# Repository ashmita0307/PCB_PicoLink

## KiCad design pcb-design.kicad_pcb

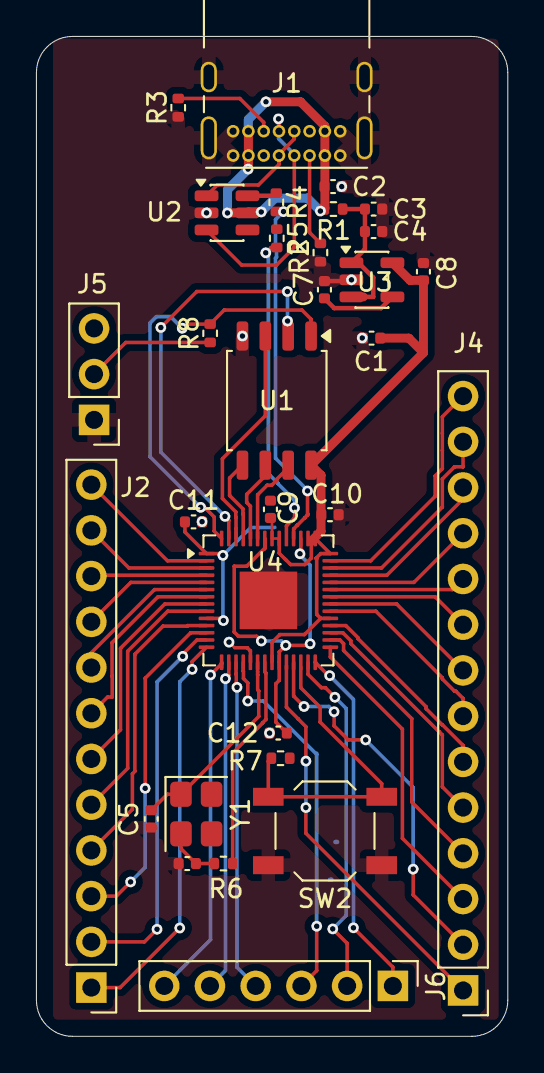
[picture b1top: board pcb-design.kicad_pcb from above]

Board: 2 copper layers, 26.2 x 55.5 mm, 31 parts (0 on the bottom side), 57 nets.

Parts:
C1: 0.1uF; C_0402_1005Metric
C2, C3, C7: 470n; C_0402_1005Metric
C4, C8: 10u; C_0402_1005Metric
C5, C6: 27pF; C_0402_1005Metric
C9, C10: 100 nF; C_0402_1005Metric
C11: 100nF; C_0402_1005Metric
C12: 1uF; C_0402_1005Metric
J1: USB_C_Receptacle_USB2.0_16P; USB_C_Receptacle_GCT_USB4085
J2: Conn_01x12; PinHeader_1x12_P2.54mm_Vertical
J4: Conn_01x14; PinHeader_1x14_P2.54mm_Vertical
J5: Conn_01x02; PinHeader_1x03_P2.54mm_Vertical
J6: Conn_01x06; PinHeader_1x06_P2.54mm_Vertical
R1: 0; R_0402_1005Metric
R2, R3: 5k1; R_0402_1005Metric
R4, R5: 27; R_0402_1005Metric
R6, R8: 1k; R_0402_1005Metric
R7: 10K; R_0402_1005Metric
SW2: SW_Push; SW_SPST_TL3342
U1: W25Q16JVSS; SOIC-8_5.3x5.3mm_P1.27mm
U2: USBLC6-2SC6; SOT-23-6
U3: SPX3819M5-L-3-3; SOT-23-5
U4: RP2040; QFN-56-1EP_7x7mm_P0.4mm_EP3.2x3.2mm
Y1: 12Mhz; Crystal_SMD_3225-4Pin_3.2x2.5mm

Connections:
+3V3: C1.1, C8.1, C9.1, C10.1, C11.1, U1.8 (VCC), U3.5 (OUT), U4.1 (IOVDD), U4.10 (IOVDD), U4.22 (IOVDD), U4.33 (IOVDD), U4.42 (IOVDD), U4.43 (ADC_AVDD), U4.44 (VREG_VIN), U4.48 (USB_VDD), U4.49 (IOVDD)
/+1V1: C12.2, U4.23 (DVDD), U4.45 (VREG_VOUT), U4.50 (DVDD)
/GPIO0: J2.12, U4.2 (GPIO0)
/GPIO1: J2.11, U4.3 (GPIO1)
/GPIO2: J2.10, U4.4 (GPIO2)
/GPIO3: J2.9, U4.5 (GPIO3)
/GPIO4: J2.8, U4.6 (GPIO4)
/GPIO5: J2.7, U4.7 (GPIO5)
/GPIO6: J2.6, U4.8 (GPIO6)
/GPIO7: J2.5, U4.9 (GPIO7)
/GPIO8: J2.4, U4.11 (GPIO8)
/GPIO9: J2.3, U4.12 (GPIO9)
/GPIO10: J2.2, U4.13 (GPIO10)
/GPIO11: J2.1, U4.14 (GPIO11)
/GPIO12: J6.6, U4.15 (GPIO12)
/GPIO13: J6.5, U4.16 (GPIO13)
/GPIO14: J6.4, U4.17 (GPIO14)
/GPIO15: J6.3, U4.18 (GPIO15)
/GPIO16: J6.2, U4.27 (GPIO16)
/GPIO17: J6.1, U4.28 (GPIO17)
/GPIO18: J4.3, U4.29 (GPIO18)
/GPIO19: J4.4, U4.30 (GPIO19)
/GPIO20: J4.5, U4.31 (GPIO20)
/GPIO21: J4.6, U4.32 (GPIO21)
/GPIO22: J4.7, U4.34 (GPIO22)
/GPIO23: J4.8, U4.35 (GPIO23)
/GPIO24: J4.9, U4.36 (GPIO24)
/GPIO25: J4.10, U4.37 (GPIO25)
/GPIO26/ADC0: J4.11, U4.38 (GPIO26/ADC0)
/GPIO27/ADC1: J4.12, U4.39 (GPIO27/ADC1)
/GPIO28/ADC2: J4.13, U4.40 (GPIO28/ADC2)
/GPIO29/ADC3: J4.14, U4.41 (GPIO29/ADC3)
/QSPI_SCLK: U1.6 (CLK), U4.52 (QSPI_SCLK)
/QSPI_SD0: U1.5 (DI/IO_{0}), U4.53 (QSPI_SD0)
/QSPI_SD1: U1.2 (DO/IO_{1}), U4.55 (QSPI_SD1)
/QSPI_SD2: U1.3 (~WP/IO_{2}), U4.54 (QSPI_SD2)
/QSPI_SD3: U1.7 (~HOLD/~RESET/IO_{3}), U4.51 (QSPI_SD3)
/QSPI_SS: R8.2, U1.1 (~CS), U4.56 (~QSPI_SS)
/SWCLK: J4.1, U4.24 (SWCLK)
/SWD: J4.2, U4.25 (SWDIO)
/USB_BOOT: J5.2, R8.1
/USB_DM: R4.2, U4.46 (USB_DM)
/USB_DP: R5.2, U4.47 (USB_DP)
/XIN: C5.1, U4.20 (XIN), Y1.1
/XOUT: R6.2, U4.21 (XOUT)
GND: C1.2, C2.2, C3.2, C4.2, C5.2, C6.1, C7.2, C8.2, C9.2, C10.2, C11.2, C12.1, J1.A1 (GND), J1.A12 (GND), J1.B1 (GND), J1.B12 (GND), J1.SH (SHIELD), J5.1, R2.1, R3.1, SW2.1, U1.4 (GND), U2.2 (GND), U3.2 (GND), U4.19 (TESTEN), U4.57 (GND)
unnamed: C6.2, R6.1, Y1.2
unnamed: J1.A5 (CC1), R2.2
unnamed: J1.B5 (CC2), R3.2
unnamed: J1.A6 (D+), J1.B6 (D+), U2.3 (I/O2)
unnamed: J1.A7 (D-), J1.B7 (D-), U2.1 (I/O1)
unnamed: R4.1, U2.6 (I/O1)
unnamed: R5.1, U2.4 (I/O2)
unnamed: C7.1, U3.4 (BP)
unnamed: R7.2, SW2.2, U4.26 (RUN)
VBUS: C2.1, J1.A4 (VBUS), J1.A9 (VBUS), J1.B4 (VBUS), J1.B9 (VBUS), R1.2, U2.5 (VBUS)
VBUSF: C3.1, C4.1, R1.1, U3.1 (IN), U3.3 (EN)

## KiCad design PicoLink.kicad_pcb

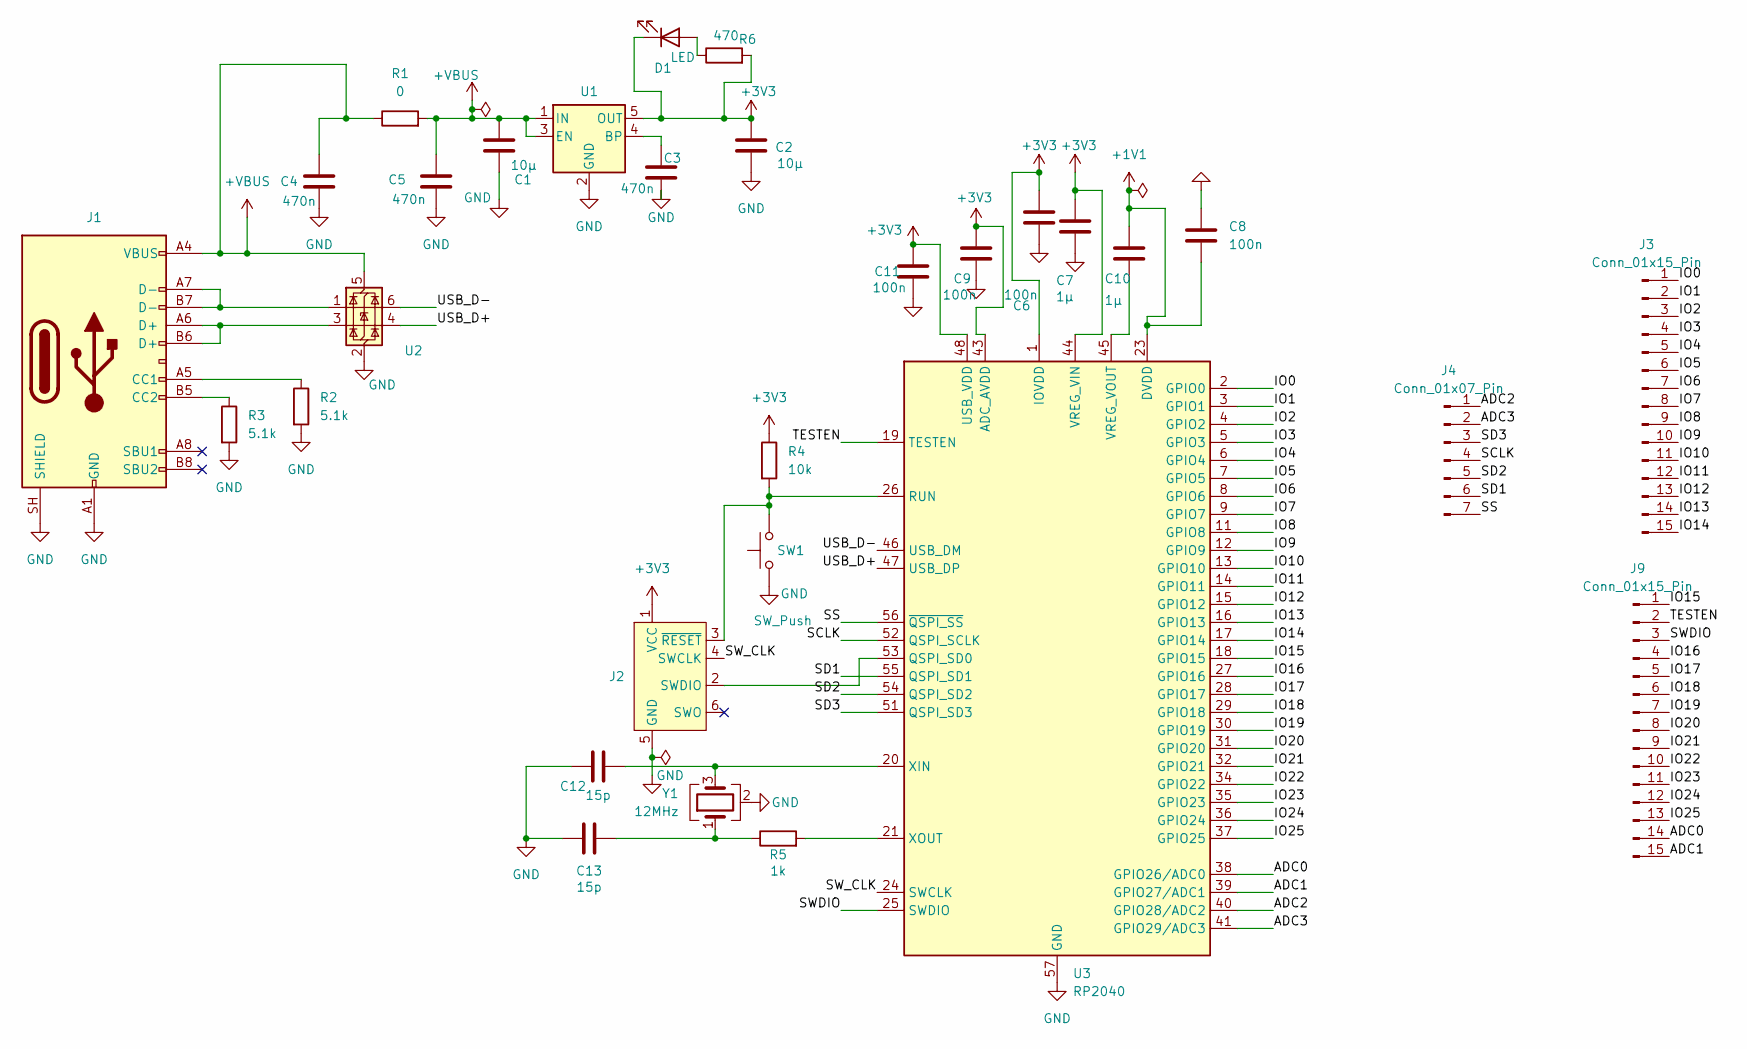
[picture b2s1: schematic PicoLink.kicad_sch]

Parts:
C1, C2: 10µ; C_0603_1608Metric
C3, C4, C5: 470n; C_0603_1608Metric
C6, C8, C9, C11: 100n; C_0603_1608Metric
C7, C10: 1µ; C_0603_1608Metric
C12, C13: 15p; C_0603_1608Metric
D1: LED; LED_0805_2012Metric
J1: USB_C_Receptacle_USB2.0_16P; USB_C_Receptacle_G-Switch_GT-USB-7010ASV
J2: Conn_ARM_SWD_TagConnect_TC2030; Tag-Connect_TC2030-IDC-FP_2x03_P1.27mm_Vertical
J3, J9: Conn_01x15_Pin; PinHeader_1x15_P2.54mm_Vertical
J4: Conn_01x07_Pin; PinHeader_1x07_P2.54mm_Vertical
R1: 0; R_0603_1608Metric
R2, R3: 5.1k; R_0603_1608Metric
R4: 10k; R_0603_1608Metric
R5: 1k; R_0603_1608Metric
R6: 470; R_0603_1608Metric
SW1: SW_Push; SW_SPST_B3U-1000P
U1: SPX3819M5-L-3-3; SOT-23-5
U2: USBLC6-2SC6; SOT-23-6
U3: RP2040; QFN-56-1EP_7x7mm_P0.4mm_EP3.2x3.2mm
Y1: 12MHz; Crystal_SMD_5032-4Pin_5.0x3.2mm

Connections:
+1V1: C8.2, C10.1, U3.23 (DVDD), U3.50 (DVDD)
+3V3: C2.1, C6.1, C7.1, C9.1, C11.1, D1.1 (K), J2.1 (VCC), R4.1, R6.2, U1.5 (OUT), U3.1 (IOVDD), U3.10 (IOVDD), U3.22 (IOVDD), U3.33 (IOVDD), U3.42 (IOVDD), U3.43 (ADC_AVDD), U3.44 (VREG_VIN), U3.48 (USB_VDD), U3.49 (IOVDD)
+VBUS: C1.1, C4.1, C5.1, J1.A4 (VBUS), J1.A9 (VBUS), J1.B4 (VBUS), J1.B9 (VBUS), R1.1, R1.2, U1.1 (IN), U1.3 (EN), U2.5 (VBUS)
/ADC0: J9.14, U3.38 (GPIO26/ADC0)
/ADC1: J9.15, U3.39 (GPIO27/ADC1)
/ADC2: J4.1, U3.40 (GPIO28/ADC2)
/ADC3: J4.2, U3.41 (GPIO29/ADC3)
/IO0: J3.1, U3.2 (GPIO0)
/IO1: J3.2, U3.3 (GPIO1)
/IO2: J3.3, U3.4 (GPIO2)
/IO3: J3.4, U3.5 (GPIO3)
/IO4: J3.5, U3.6 (GPIO4)
/IO5: J3.6, U3.7 (GPIO5)
/IO6: J3.7, U3.8 (GPIO6)
/IO7: J3.8, U3.9 (GPIO7)
/IO8: J3.9, U3.11 (GPIO8)
/IO9: J3.10, U3.12 (GPIO9)
/IO10: J3.11, U3.13 (GPIO10)
/IO11: J3.12, U3.14 (GPIO11)
/IO12: J3.13, U3.15 (GPIO12)
/IO13: J3.14, U3.16 (GPIO13)
/IO14: J3.15, U3.17 (GPIO14)
/IO15: J9.1, U3.18 (GPIO15)
/IO16: J9.4, U3.27 (GPIO16)
/IO17: J9.5, U3.28 (GPIO17)
/IO18: J9.6, U3.29 (GPIO18)
/IO19: J9.7, U3.30 (GPIO19)
/IO20: J9.8, U3.31 (GPIO20)
/IO21: J9.9, U3.32 (GPIO21)
/IO22: J9.10, U3.34 (GPIO22)
/IO23: J9.11, U3.35 (GPIO23)
/IO24: J9.12, U3.36 (GPIO24)
/IO25: J9.13, U3.37 (GPIO25)
/SCLK: J4.4, U3.52 (QSPI_SCLK)
/SD1: J4.6, U3.55 (QSPI_SD1)
/SD2: J4.5, U3.54 (QSPI_SD2)
/SD3: J4.3, U3.51 (QSPI_SD3)
/SS: J4.7, U3.56 (~QSPI_SS)
/SWDIO: J9.3, U3.25 (SWDIO)
/SW_CLK: J2.4 (SWCLK), U3.24 (SWCLK)
/TESTEN: J9.2, U3.19 (TESTEN)
/USB_D+: U2.4 (I/O2), U3.47 (USB_DP)
/USB_D-: U2.6 (I/O1), U3.46 (USB_DM)
GND: C1.2, C2.2, C3.2, C4.2, C5.2, C6.2, C7.2, C8.1, C9.2, C11.2, C12.1, C13.1, J1.A1 (GND), J1.A12 (GND), J1.B1 (GND), J1.B12 (GND), J1.SH (SHIELD), J2.5 (GND), R2.2, R3.2, SW1.1, U1.2 (GND), U2.2 (GND), U3.57 (GND), Y1.2 (G), Y1.4 (G)
unnamed: C13.2, R5.1, Y1.1
unnamed: D1.2 (A), R6.1
unnamed: J1.A5 (CC1), R2.1
unnamed: J1.B5 (CC2), R3.1
unnamed: J1.A6 (D+), J1.B6 (D+), U2.3 (I/O2)
unnamed: J1.A7 (D-), J1.B7 (D-), U2.1 (I/O1)
unnamed: J2.2 (SWDIO), U3.53 (QSPI_SD0)
unnamed: J2.3 (~RESET), R4.2, SW1.2, U3.26 (RUN)
unnamed: C3.1, U1.4 (BP)
unnamed: C10.2, U3.45 (VREG_VOUT)
unnamed: C12.2, U3.20 (XIN), Y1.3
unnamed: R5.2, U3.21 (XOUT)

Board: 2 copper layers, 30 parts (0 on the bottom side), 56 nets, no tracks yet.
